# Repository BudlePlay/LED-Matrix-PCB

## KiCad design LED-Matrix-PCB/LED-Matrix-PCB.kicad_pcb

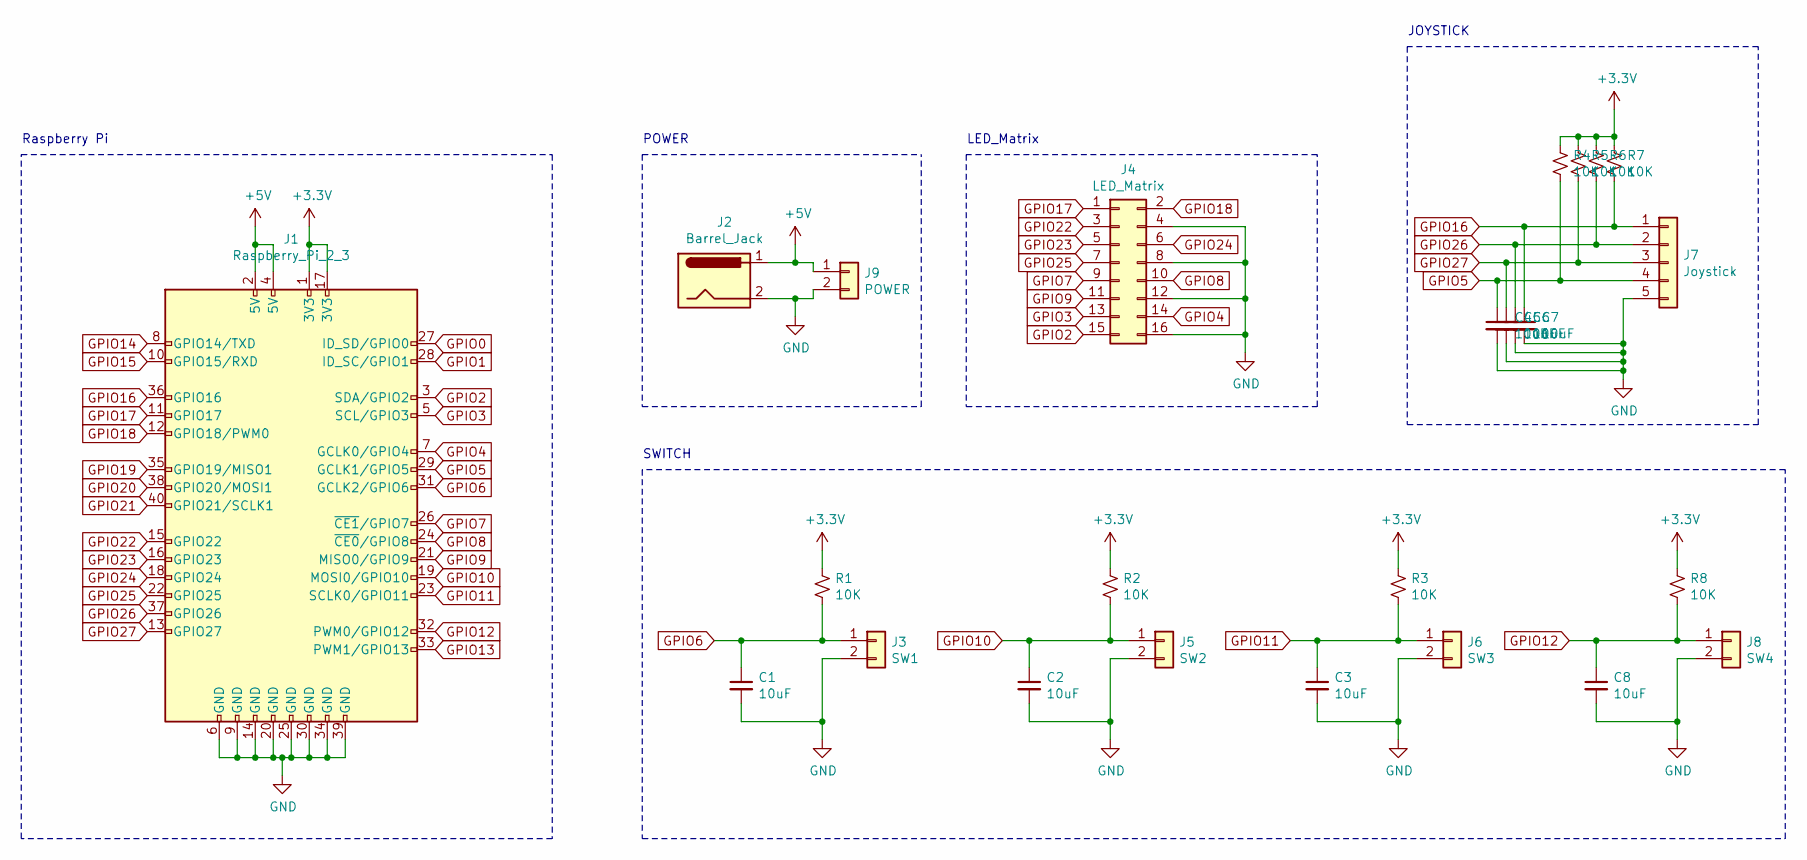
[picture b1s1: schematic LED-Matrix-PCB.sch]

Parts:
C1, C2, C3, C4, C5, C6, C7, C8: 10uF; C_0603_1608Metric
J1: Raspberry_Pi_2_3; PinHeader_2x20_P2.54mm_Vertical
J2: Barrel_Jack; BarrelJack_CUI_PJ-063AH_Horizontal
J3: SW1; Molex_SPOX_5267-02A_1x02_P2.50mm_Vertical
J4: LED_Matrix; IDC-Header_2x08_P2.54mm_Vertical
J5: SW2; Molex_SPOX_5267-02A_1x02_P2.50mm_Vertical
J6: SW3; Molex_SPOX_5267-02A_1x02_P2.50mm_Vertical
J7: Joystick; Molex_SPOX_5267-05A_1x05_P2.50mm_Vertical
J8: SW4; Molex_SPOX_5267-02A_1x02_P2.50mm_Vertical
J9: POWER; Molex_SPOX_5267-02A_1x02_P2.50mm_Vertical
R1, R2, R3, R4, R5, R6, R7, R8: 10K; R_0603_1608Metric

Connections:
+3V3: J1.1 (3V3), J1.17 (3V3), R1.1, R2.1, R3.1, R4.1, R5.1, R6.1, R7.1, R8.1
+5V: J1.2 (5V), J1.4 (5V), J2.1, J9.1; also elsewhere on the board
GND: C1.2, C2.2, C3.2, C4.2, C5.2, C6.2, C7.2, C8.2, J1.6 (GND), J1.9 (GND), J1.14 (GND), J1.20 (GND), J1.25 (GND), J1.30 (GND), J1.34 (GND), J1.39 (GND), J2.2, J3.2, J4.4, J4.8, J4.12, J4.16, J5.2, J6.2, J7.5, J8.2, J9.2; also elsewhere on the board
GPIO0: J1.27 (ID_SD/GPIO0)
GPIO1: J1.28 (ID_SC/GPIO1)
GPIO2: J1.3 (SDA/GPIO2), J4.15; also elsewhere on the board
GPIO3: J1.5 (SCL/GPIO3), J4.13; also elsewhere on the board
GPIO4: J1.7 (GCLK0/GPIO4), J4.14; also elsewhere on the board
GPIO5: C4.1, J1.29 (GCLK1/GPIO5), J7.4, R4.2
GPIO6: C1.1, J1.31 (GCLK2/GPIO6), J3.1, R1.2
GPIO7: J1.26 (~CE1~/GPIO7), J4.9; also elsewhere on the board
GPIO8: J1.24 (~CE0~/GPIO8), J4.10; also elsewhere on the board
GPIO9: J1.21 (MISO0/GPIO9), J4.11; also elsewhere on the board
GPIO10: C2.1, J1.19 (MOSI0/GPIO10), J5.1, R2.2
GPIO11: C3.1, J1.23 (SCLK0/GPIO11), J6.1, R3.2
GPIO12: C8.1, J1.32 (PWM0/GPIO12), J8.1, R8.2
GPIO13: J1.33 (PWM1/GPIO13)
GPIO14: J1.8 (GPIO14/TXD)
GPIO15: J1.10 (GPIO15/RXD)
GPIO16: C7.1, J1.36 (GPIO16), J7.1, R7.2
GPIO17: J1.11 (GPIO17), J4.1; also elsewhere on the board
GPIO18: J1.12 (GPIO18/PWM0), J4.2; also elsewhere on the board
GPIO19: J1.35 (GPIO19/MISO1)
GPIO20: J1.38 (GPIO20/MOSI1)
GPIO21: J1.40 (GPIO21/SCLK1)
GPIO22: J1.15 (GPIO22), J4.3; also elsewhere on the board
GPIO23: J1.16 (GPIO23), J4.5; also elsewhere on the board
GPIO24: J1.18 (GPIO24), J4.6; also elsewhere on the board
GPIO25: J1.22 (GPIO25), J4.7; also elsewhere on the board
GPIO26: C6.1, J1.37 (GPIO26), J7.2, R6.2
GPIO27: C5.1, J1.13 (GPIO27), J7.3, R5.2

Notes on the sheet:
Raspberry Pi
POWER
SWITCH
LED_Matrix
JOYSTICK

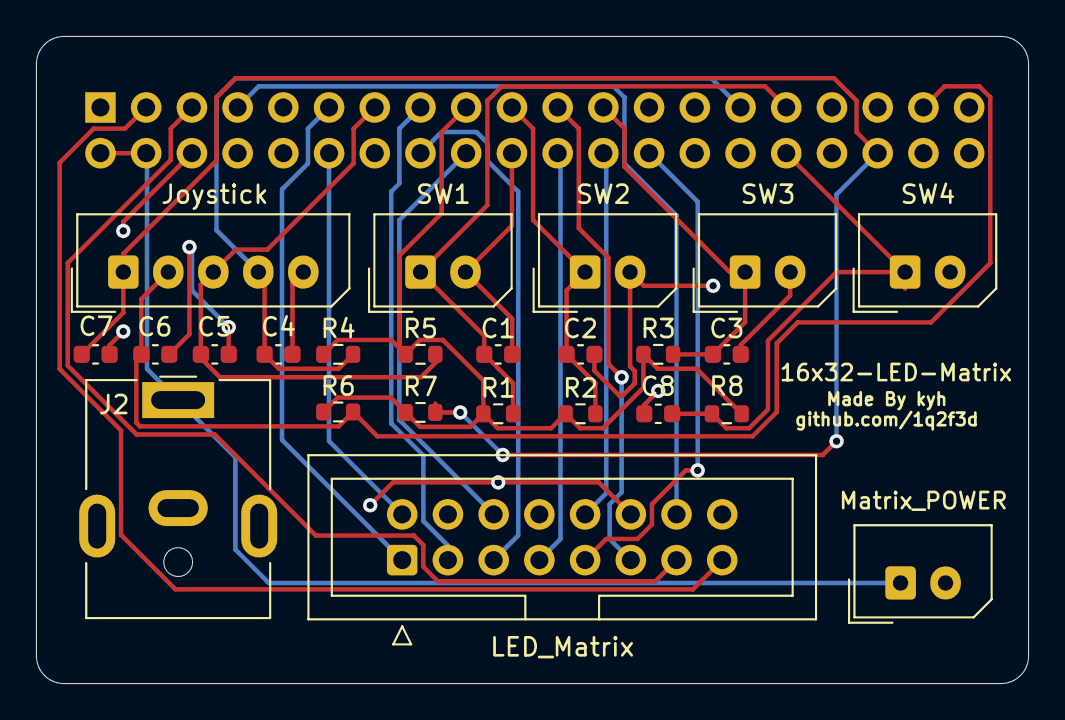
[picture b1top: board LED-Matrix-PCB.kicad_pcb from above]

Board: 2 copper layers, 55.1 x 36.0 mm, 25 parts (1 on the bottom side), 23 nets.

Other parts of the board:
LED_Matrix: LED_Matrix; IDC-Header_2x08_P2.54mm_Vertical
Matrix_POWER: POWER; Molex_SPOX_5267-02A_1x02_P2.50mm_Vertical

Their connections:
+5V: Matrix_POWER.1; also elsewhere on the board
GND: LED_Matrix.4, LED_Matrix.8, LED_Matrix.12, LED_Matrix.16, Matrix_POWER.2; also elsewhere on the board
GPIO2: LED_Matrix.15; also elsewhere on the board
GPIO3: LED_Matrix.13; also elsewhere on the board
GPIO4: LED_Matrix.14; also elsewhere on the board
GPIO7: LED_Matrix.9; also elsewhere on the board
GPIO8: LED_Matrix.10; also elsewhere on the board
GPIO9: LED_Matrix.11; also elsewhere on the board
GPIO17: LED_Matrix.1; also elsewhere on the board
GPIO18: LED_Matrix.2; also elsewhere on the board
GPIO22: LED_Matrix.3; also elsewhere on the board
GPIO23: LED_Matrix.5; also elsewhere on the board
GPIO24: LED_Matrix.6; also elsewhere on the board
GPIO25: LED_Matrix.7; also elsewhere on the board

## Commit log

2021-04-26 Circuit Complete
2021-05-20 Complete
2021-05-25 Add Gerber Files
